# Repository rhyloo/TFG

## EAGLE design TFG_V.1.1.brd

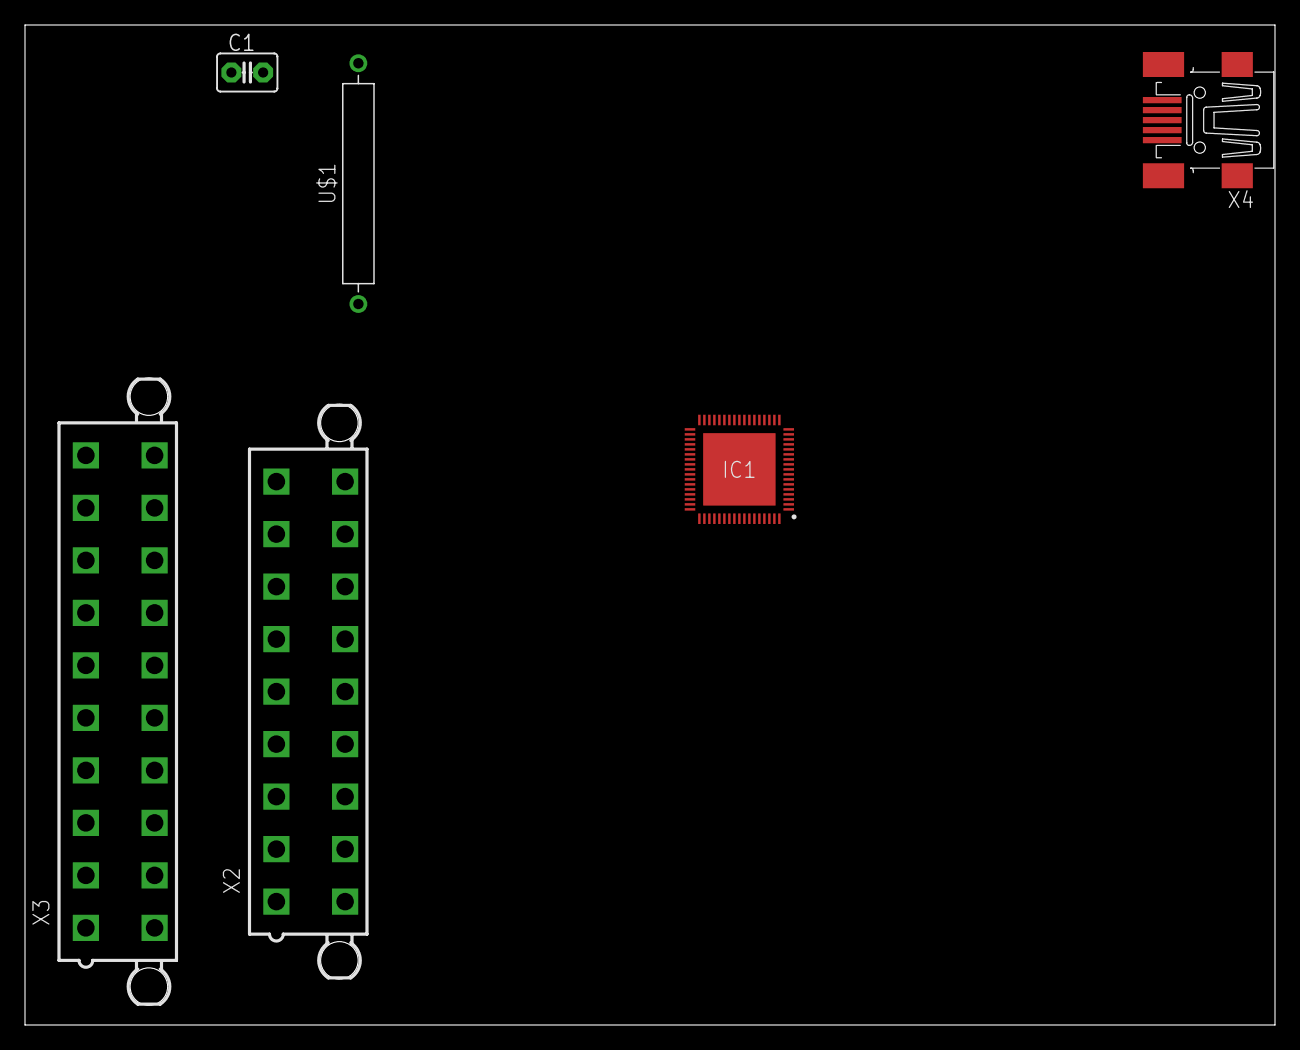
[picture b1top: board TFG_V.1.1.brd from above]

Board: 2 copper layers, 100.0 x 80.0 mm, 6 parts (0 on the bottom side), 7 nets, no tracks yet.

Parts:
C1: 0.1uF; C2.5-3
IC1: CY8C4248LTQ-L485; QFN40P800X800X100-69N
U$1: FUSE; FUSAD1926W63L1550D250B
X2: 5566-18
X3: 5566-20
X4: MINI-USB-32005-201; 32005-201

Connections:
DM: IC1.37, X4.2
DP: IC1.36, X4.3
GND: C1.2, X2.18, X3.20, X4.5
I2C_SCL: IC1.46, X2.17, X3.19
I2C_SDA: IC1.47, X2.16, X3.18
unnamed: C1.1, U$1.2, X4.1
VCC: IC1.38, U$1.1, X2.15, X3.17

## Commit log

2023-03-16 Init
    Inicio del esquemático del TFG
2023-03-16 Create CY8C4248LTQ-L485.lbr
    Librería añadida
2023-03-16 Libreria actualizada
    He actualizado el símbolo del PSoC para facilitar las conexiones en el esquemático
2023-03-16 PSoC añadido al esquematico
2023-03-16 Grid activado
2023-03-28 Mapeado de puertos
    Mapeado de puertos de los sensores y protocolos de comunicación. Añadido un intento de conexión USB.
2023-03-28 Nombre de los puertos
2023-03-28 Pruebas sobre una PCB
2023-03-28 Extracto de la PCB
